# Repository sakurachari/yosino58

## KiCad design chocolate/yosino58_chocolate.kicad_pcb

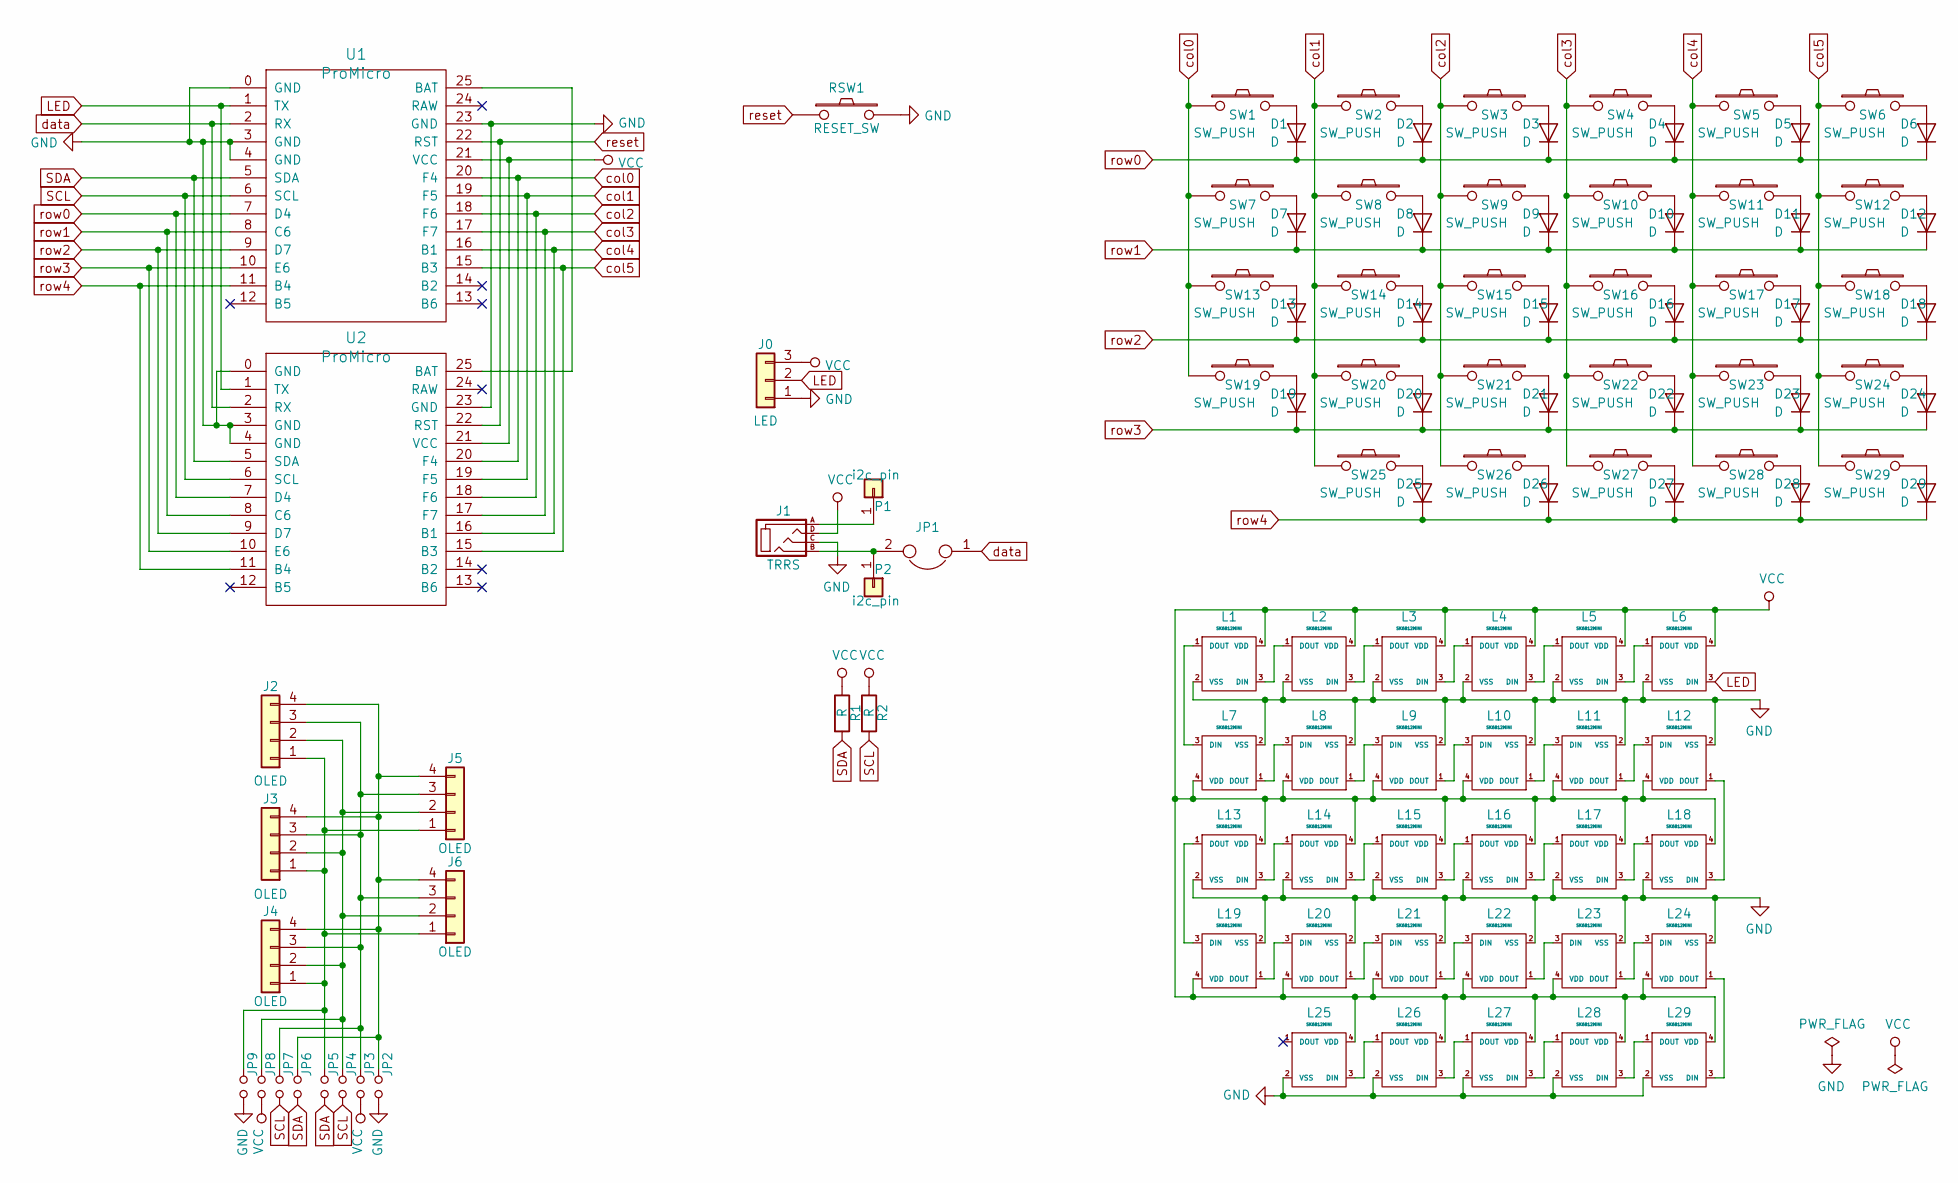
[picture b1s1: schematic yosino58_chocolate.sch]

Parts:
D1, D2, D3, D4, D5, D6, D7, D8, D9, D10, D11, D12, D13, D14, D15, D16, D17, D18, D19, D20, D21, D22, D23, D24, D25, D26, D27, D28, D29: D; D3_TH_SMD
J0: LED; StripLED_rev
J1: TRRS; MJ-4PP-9
J2, J3, J4, J5, J6: OLED
JP1: Jumper; JPC2
JP2, JP9: GND; Jumper
JP3, JP8: VCC; Jumper
JP4, JP7: SCL; Jumper
JP5, JP6: SDA; Jumper
L1, L2, L3, L4, L5, L6, L7, L8, L9, L10, L11, L12, L13, L14, L15, L16, L17, L18, L19, L20, L21, L22, L23, L24, L25, L26, L27, L28, L29: SK6812MINI; SK6812MINI_rev
P1, P2: i2c_pin; 1pin_conn
R1, R2: R
RSW1: RESET_SW; ResetSW
SW1, SW2, SW3, SW4, SW5, SW6, SW7, SW8, SW9, SW10, SW11, SW12, SW13, SW14, SW15, SW16, SW17, SW18, SW19, SW20, SW21, SW22, SW23, SW24, SW25, SW26, SW27, SW28: SW_PUSH; Choc_Hotswap
SW29: SW_PUSH; Choc_Hotswap2U_stabilizer
U1, U2: ProMicro; ProMicro_BLE

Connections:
GND: J0.1, J1.C, JP2.2, JP9.2, L1.2 (VSS), L2.2 (VSS), L3.2 (VSS), L4.2 (VSS), L5.2 (VSS), L6.2 (VSS), L7.2 (VSS), L8.2 (VSS), L9.2 (VSS), L10.2 (VSS), L11.2 (VSS), L12.2 (VSS), L13.2 (VSS), L14.2 (VSS), L15.2 (VSS), L16.2 (VSS), L17.2 (VSS), L18.2 (VSS), L19.2 (VSS), L20.2 (VSS), L21.2 (VSS), L22.2 (VSS), L23.2 (VSS), L24.2 (VSS), L25.2 (VSS), L26.2 (VSS), L27.2 (VSS), L28.2 (VSS), L29.2 (VSS), RSW1.2, U1.0 (GND), U1.3 (GND), U1.4 (GND), U1.23 (GND), U2.0 (GND), U2.3 (GND), U2.4 (GND), U2.23 (GND)
LED: J0.2, L6.3 (DIN), U1.1 (TX), U2.1 (TX)
unnamed: D1.2 (A), SW1.2
unnamed: D2.2 (A), SW2.2
unnamed: D3.2 (A), SW3.2
unnamed: D4.2 (A), SW4.2
unnamed: D5.2 (A), SW5.2
unnamed: D6.2 (A), SW6.2
unnamed: D7.2 (A), SW7.2
unnamed: D8.2 (A), SW8.2
unnamed: D9.2 (A), SW9.2
unnamed: D10.2 (A), SW10.2
unnamed: D11.2 (A), SW11.2
unnamed: D12.2 (A), SW12.2
unnamed: D13.2 (A), SW13.2
unnamed: D14.2 (A), SW14.2
unnamed: D15.2 (A), SW15.2
unnamed: D16.2 (A), SW16.2
unnamed: D17.2 (A), SW17.2
unnamed: D18.2 (A), SW18.2
unnamed: D19.2 (A), SW19.2
unnamed: D20.2 (A), SW20.2
unnamed: D21.2 (A), SW21.2
unnamed: D22.2 (A), SW22.2
unnamed: D23.2 (A), SW23.2
unnamed: D24.2 (A), SW24.2
unnamed: D25.2 (A), SW25.2
unnamed: D26.2 (A), SW26.2
unnamed: D27.2 (A), SW27.2
unnamed: D28.2 (A), SW28.2
unnamed: D29.2 (A), SW29.2
unnamed: J1.A, P1.1
unnamed: J1.B, JP1.2, P2.1
unnamed: J2.1, J3.1, J4.1, J5.1, J6.1, JP5.1, JP9.1
unnamed: J2.2, J3.2, J4.2, J5.2, J6.2, JP4.1, JP8.1
unnamed: J2.3, J3.3, J4.3, J5.3, J6.3, JP3.1, JP7.1
unnamed: J2.4, J3.4, J4.4, J5.4, J6.4, JP2.1, JP6.1
unnamed: L1.1 (DOUT), L7.3 (DIN)
unnamed: L1.3 (DIN), L2.1 (DOUT)
unnamed: L2.3 (DIN), L3.1 (DOUT)
unnamed: L3.3 (DIN), L4.1 (DOUT)
unnamed: L4.3 (DIN), L5.1 (DOUT)
unnamed: L5.3 (DIN), L6.1 (DOUT)
unnamed: L7.1 (DOUT), L8.3 (DIN)
unnamed: L8.1 (DOUT), L9.3 (DIN)
unnamed: L10.1 (DOUT), L11.3 (DIN)
unnamed: L9.1 (DOUT), L10.3 (DIN)
unnamed: L11.1 (DOUT), L12.3 (DIN)
unnamed: L12.1 (DOUT), L18.3 (DIN)
unnamed: L13.1 (DOUT), L19.3 (DIN)
unnamed: L13.3 (DIN), L14.1 (DOUT)
unnamed: L14.3 (DIN), L15.1 (DOUT)
unnamed: L15.3 (DIN), L16.1 (DOUT)
unnamed: L16.3 (DIN), L17.1 (DOUT)
unnamed: L17.3 (DIN), L18.1 (DOUT)
unnamed: L19.1 (DOUT), L20.3 (DIN)
unnamed: L20.1 (DOUT), L21.3 (DIN)
unnamed: L21.1 (DOUT), L22.3 (DIN)
unnamed: L22.1 (DOUT), L23.3 (DIN)
unnamed: L23.1 (DOUT), L24.3 (DIN)
unnamed: L24.1 (DOUT), L29.3 (DIN)
unnamed: L25.3 (DIN), L26.1 (DOUT)
unnamed: L26.3 (DIN), L27.1 (DOUT)
unnamed: L27.3 (DIN), L28.1 (DOUT)
unnamed: L28.3 (DIN), L29.1 (DOUT)
unnamed: U1.25 (BAT), U2.25 (BAT)
SCL: JP4.2, JP7.2, R2.2, U1.6 (SCL), U2.6 (SCL)
SDA: JP5.2, JP6.2, R1.2, U1.5 (SDA), U2.5 (SDA)
VCC: J0.3, J1.D, JP3.2, JP8.2, L1.4 (VDD), L2.4 (VDD), L3.4 (VDD), L4.4 (VDD), L5.4 (VDD), L6.4 (VDD), L7.4 (VDD), L8.4 (VDD), L9.4 (VDD), L10.4 (VDD), L11.4 (VDD), L12.4 (VDD), L13.4 (VDD), L14.4 (VDD), L15.4 (VDD), L16.4 (VDD), L17.4 (VDD), L18.4 (VDD), L19.4 (VDD), L20.4 (VDD), L21.4 (VDD), L22.4 (VDD), L23.4 (VDD), L24.4 (VDD), L25.4 (VDD), L26.4 (VDD), L27.4 (VDD), L28.4 (VDD), L29.4 (VDD), R1.1, R2.1, U1.21 (VCC), U2.21 (VCC)
col0: SW1.1, SW7.1, SW13.1, SW19.1, U1.20 (F4), U2.20 (F4)
col1: SW2.1, SW8.1, SW14.1, SW20.1, SW25.1, U1.19 (F5), U2.19 (F5)
col2: SW3.1, SW9.1, SW15.1, SW21.1, SW26.1, U1.18 (F6), U2.18 (F6)
col3: SW4.1, SW10.1, SW16.1, SW22.1, SW27.1, U1.17 (F7), U2.17 (F7)
col4: SW5.1, SW11.1, SW17.1, SW23.1, SW28.1, U1.16 (B1), U2.16 (B1)
col5: SW6.1, SW12.1, SW18.1, SW24.1, SW29.1, U1.15 (B3), U2.15 (B3)
data: JP1.1, U1.2 (RX), U2.2 (RX)
reset: RSW1.1, U1.22 (RST), U2.22 (RST)
row0: D1.1 (K), D2.1 (K), D3.1 (K), D4.1 (K), D5.1 (K), D6.1 (K), U1.7 (D4), U2.7 (D4)
row1: D7.1 (K), D8.1 (K), D9.1 (K), D10.1 (K), D11.1 (K), D12.1 (K), U1.8 (C6), U2.8 (C6)
row2: D13.1 (K), D14.1 (K), D15.1 (K), D16.1 (K), D17.1 (K), D18.1 (K), U1.9 (D7), U2.9 (D7)
row3: D19.1 (K), D20.1 (K), D21.1 (K), D22.1 (K), D23.1 (K), D24.1 (K), U1.10 (E6), U2.10 (E6)
row4: D25.1 (K), D26.1 (K), D27.1 (K), D28.1 (K), D29.1 (K), U1.11 (B4), U2.11 (B4)

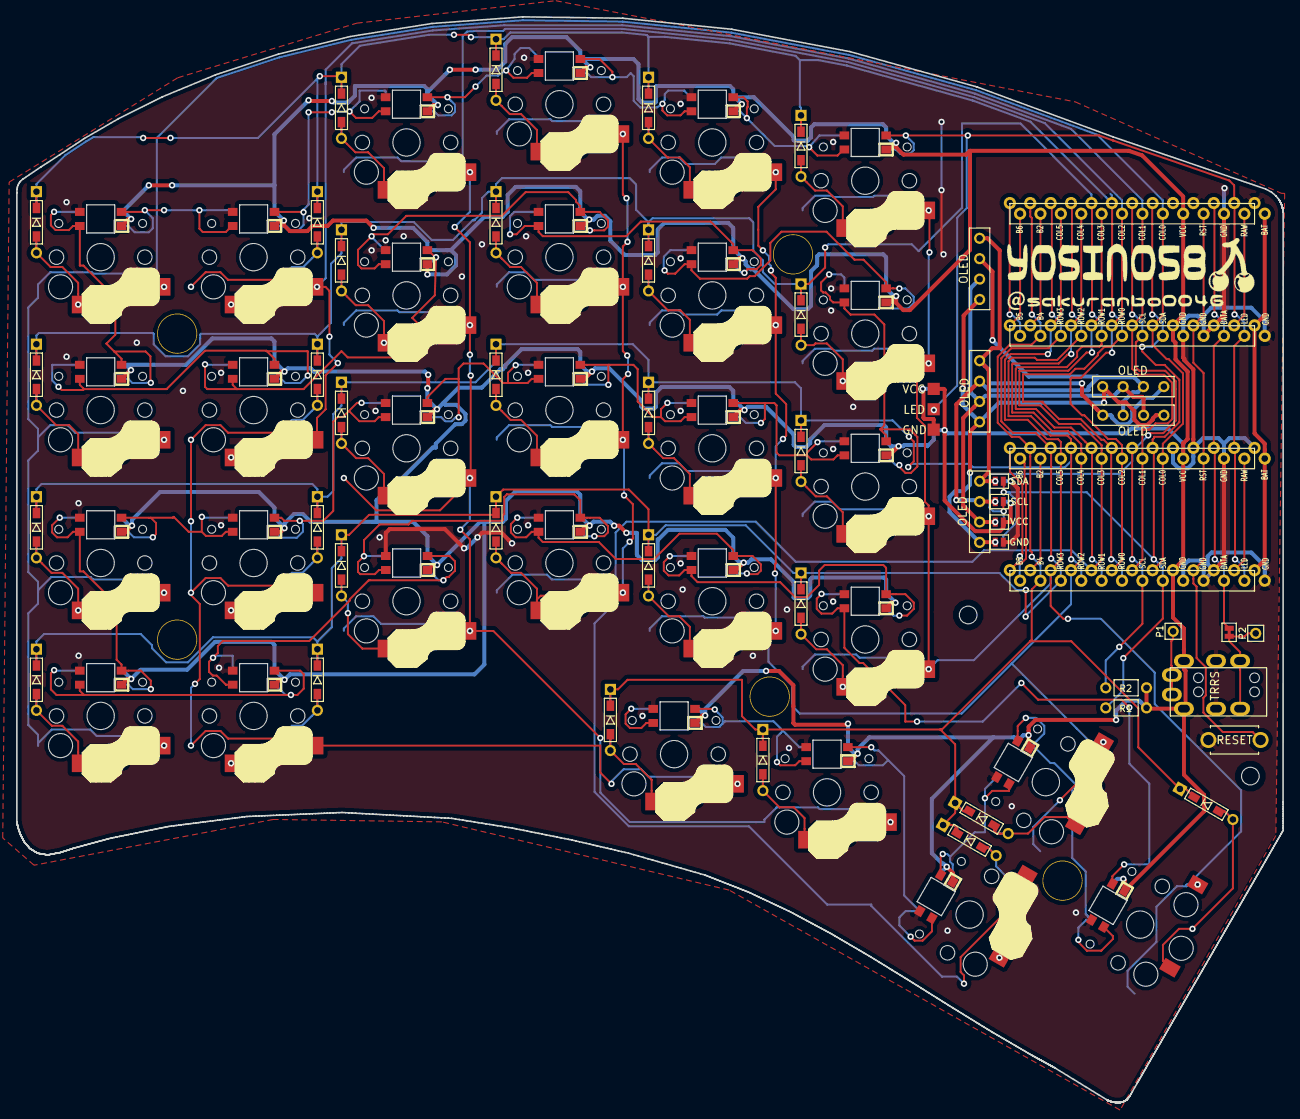
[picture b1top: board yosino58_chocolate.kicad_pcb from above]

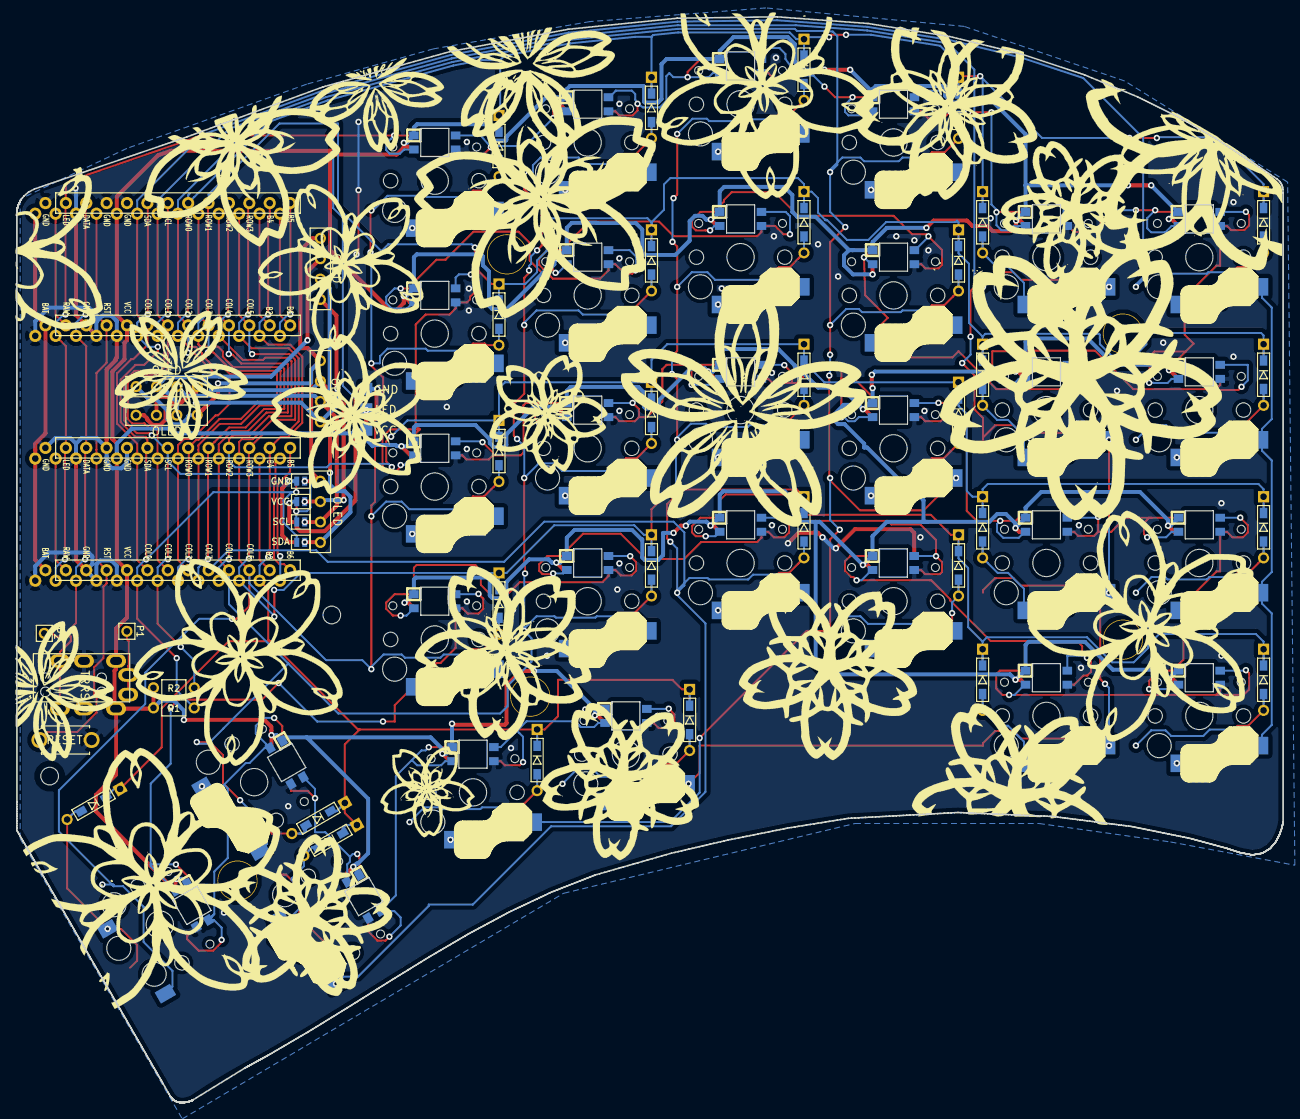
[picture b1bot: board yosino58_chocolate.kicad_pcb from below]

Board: 2 copper layers, 157.8 x 135.3 mm, 117 parts (4 on the bottom side), 82 nets.

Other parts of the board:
HOLE_M2, HOLE_M2#2: VAL**; M2_HOLE
Ref**: Val**; spacer
Ref**#2, Ref**#3, Ref**#4, Ref**#5: Val**; spacer

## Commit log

2019-03-21 ビルドガイド作成
2019-03-22 ケース作成
2019-03-22 pcb作成
2019-03-26 ビルドガイド作成
2019-04-04 SK6812MINIの外形修正
2019-04-12 qmk部分修正
2019-04-23 スイッチ取付の説明修正
2019-04-28 LED点灯順追加
2019-05-14 ソケット版追加
2019-05-22 基本外形修正
2019-05-22 Logo画像追加
